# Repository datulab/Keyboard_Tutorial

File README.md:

# Keyboard_Tutorial
All the files needed to build your first DIY keyboard! 
Watch the videos here: https://youtu.be/ajjujZ0f_sk

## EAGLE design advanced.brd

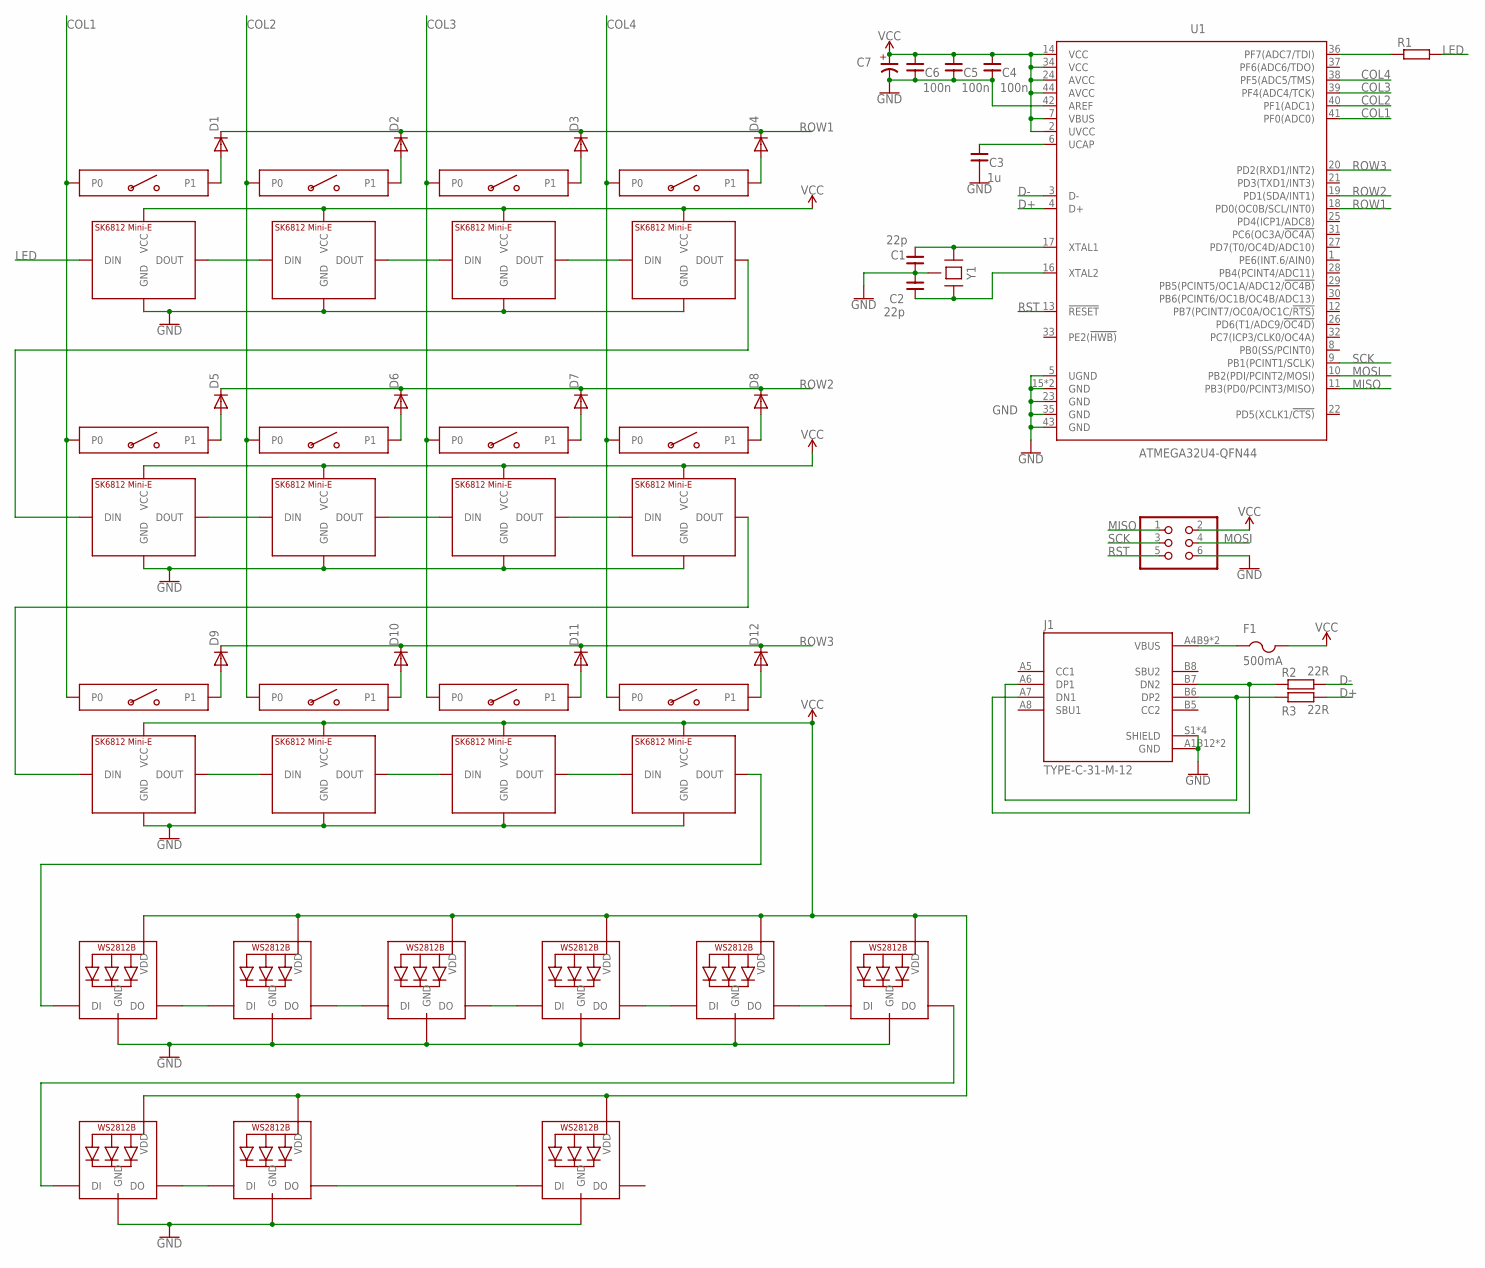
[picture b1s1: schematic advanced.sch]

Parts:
C1, C2: 22p; 0805
C3: 1u; 0805
C4, C5, C6: 100n; 0805
C7: 10u; 3216-18R/T
D1, D2, D3, D4, D5, D6, D7, D8, D9, D10, D11, D12: 1N4148DIODE_0805; 0805
F1: 500mA; R1206
J1: TYPE-C-31-M-12; HRO_TYPE-C-31-M-12
JP3: PINHD-2X3; 2X03
R1: RESISTOR-0805; R0805
R2, R3: 22R; R0805
U1: ATMEGA32U4-QFN44; QFN-44
U$1, U$2, U$3, U$4, U$5, U$6, U$7, U$8, U$10: WS2812B-3535; 3535-LED
U$55, U$57, U$59, U$61, U$73, U$75, U$77, U$79, U$91, U$93, U$95, U$97: KEYSWITCH-SK6812; UNIVERSAL_KEYSWITCH_SK6812MINIE
Y1: CRYSTAL-4PIN-3.2X2.5; CRYSTAL-3.2X2.5

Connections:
COL1: U1.41 (PF0(ADC0)), U$55.ALPS1 (P0), U$55.CHOC1 (P0), U$55.MX1 (P0), U$73.ALPS1 (P0), U$73.CHOC1 (P0), U$73.MX1 (P0), U$91.ALPS1 (P0), U$91.CHOC1 (P0), U$91.MX1 (P0)
COL2: U1.40 (PF1(ADC1)), U$57.ALPS1 (P0), U$57.CHOC1 (P0), U$57.MX1 (P0), U$75.ALPS1 (P0), U$75.CHOC1 (P0), U$75.MX1 (P0), U$93.ALPS1 (P0), U$93.CHOC1 (P0), U$93.MX1 (P0)
COL3: U1.39 (PF4(ADC4/TCK)), U$59.ALPS1 (P0), U$59.CHOC1 (P0), U$59.MX1 (P0), U$77.ALPS1 (P0), U$77.CHOC1 (P0), U$77.MX1 (P0), U$95.ALPS1 (P0), U$95.CHOC1 (P0), U$95.MX1 (P0)
COL4: U1.38 (PF5(ADC5/TMS)), U$61.ALPS1 (P0), U$61.CHOC1 (P0), U$61.MX1 (P0), U$79.ALPS1 (P0), U$79.CHOC1 (P0), U$79.MX1 (P0), U$97.ALPS1 (P0), U$97.CHOC1 (P0), U$97.MX1 (P0)
D+: R3.2, U1.4 (D+)
D-: R2.2, U1.3 (D-)
GND: C1.1, C2.2, C3.2, C4.2, C5.2, C6.2, C7.-, J1.A1B12 (GND), J1.B1A12 (GND), J1.S1 (SHIELD), J1.S2 (SHIELD), J1.S3 (SHIELD), J1.S4 (SHIELD), JP3.6, U1.5 (UGND), U1.15 (GND), U1.23 (GND), U1.35 (GND), U1.42 (AREF), U1.43 (GND), U1.TAB (GND), U$1.GND, U$2.GND, U$3.GND, U$4.GND, U$5.GND, U$6.GND, U$7.GND, U$8.GND, U$10.GND, U$55.GND, U$57.GND, U$59.GND, U$61.GND, U$73.GND, U$75.GND, U$77.GND, U$79.GND, U$91.GND, U$93.GND, U$95.GND, U$97.GND, Y1.2 (GND), Y1.4 (GND)
LED: R1.2, U$91.DIN
MISO: JP3.1, U1.11 (PB3(PD0/PCINT3/MISO))
MOSI: JP3.4, U1.10 (PB2(PDI/PCINT2/MOSI))
unnamed: U$1.P$4 (DO), U$2.P$3 (DI)
unnamed: U$2.P$4 (DO), U$3.P$3 (DI)
unnamed: U$3.P$4 (DO), U$4.P$3 (DI)
unnamed: U$4.P$4 (DO), U$5.P$3 (DI)
unnamed: U$5.P$4 (DO), U$6.P$3 (DI)
unnamed: U$7.P$4 (DO), U$8.P$3 (DI)
unnamed: U$8.P$4 (DO), U$10.P$3 (DI)
unnamed: U$6.P$4 (DO), U$7.P$3 (DI)
unnamed: U$1.P$3 (DI), U$61.DOUT
unnamed: C1.2, U1.17 (XTAL1), Y1.1
unnamed: F1.1, J1.A4B9 (VBUS), J1.B4A9 (VBUS)
unnamed: R1.1, U1.36 (PF7(ADC7/TDI))
unnamed: J1.A6 (DP1), J1.B6 (DP2), R3.1
unnamed: C2.1, U1.16 (XTAL2), Y1.3 (2)
unnamed: J1.A7 (DN1), J1.B7 (DN2), R2.1
unnamed: C3.1, U1.6 (UCAP)
unnamed: D9.1 (A), U$55.ALPS2 (P1), U$55.CHOC2 (P1), U$55.MX2 (P1)
unnamed: D10.1 (A), U$57.ALPS2 (P1), U$57.CHOC2 (P1), U$57.MX2 (P1)
unnamed: D11.1 (A), U$59.ALPS2 (P1), U$59.CHOC2 (P1), U$59.MX2 (P1)
unnamed: D12.1 (A), U$61.ALPS2 (P1), U$61.CHOC2 (P1), U$61.MX2 (P1)
unnamed: U$55.DOUT, U$57.DIN
unnamed: U$57.DOUT, U$59.DIN
unnamed: U$59.DOUT, U$61.DIN
unnamed: D5.1 (A), U$73.ALPS2 (P1), U$73.CHOC2 (P1), U$73.MX2 (P1)
unnamed: D6.1 (A), U$75.ALPS2 (P1), U$75.CHOC2 (P1), U$75.MX2 (P1)
unnamed: D7.1 (A), U$77.ALPS2 (P1), U$77.CHOC2 (P1), U$77.MX2 (P1)
unnamed: D8.1 (A), U$79.ALPS2 (P1), U$79.CHOC2 (P1), U$79.MX2 (P1)
unnamed: U$73.DOUT, U$75.DIN
unnamed: U$75.DOUT, U$77.DIN
unnamed: U$77.DOUT, U$79.DIN
unnamed: D1.1 (A), U$91.ALPS2 (P1), U$91.CHOC2 (P1), U$91.MX2 (P1)
unnamed: D2.1 (A), U$93.ALPS2 (P1), U$93.CHOC2 (P1), U$93.MX2 (P1)
unnamed: D3.1 (A), U$95.ALPS2 (P1), U$95.CHOC2 (P1), U$95.MX2 (P1)
unnamed: D4.1 (A), U$97.ALPS2 (P1), U$97.CHOC2 (P1), U$97.MX2 (P1)
unnamed: U$91.DOUT, U$93.DIN
unnamed: U$93.DOUT, U$95.DIN
unnamed: U$95.DOUT, U$97.DIN
unnamed: U$55.DIN, U$79.DOUT
unnamed: U$73.DIN, U$97.DOUT
ROW1: D1.2 (C), D2.2 (C), D3.2 (C), D4.2 (C), U1.18 (PD0(OC0B/SCL/INT0))
ROW2: D5.2 (C), D6.2 (C), D7.2 (C), D8.2 (C), U1.19 (PD1(SDA/INT1))
ROW3: D9.2 (C), D10.2 (C), D11.2 (C), D12.2 (C), U1.20 (PD2(RXD1/INT2))
RST: JP3.5, U1.13 (!RESET)
SCK: JP3.3, U1.9 (PB1(PCINT1/SCLK))
VCC: C4.1, C5.1, C6.1, C7.+, F1.2, JP3.2, U1.2 (UVCC), U1.7 (VBUS), U1.14 (VCC), U1.24 (AVCC), U1.34 (VCC), U1.44 (AVCC), U$1.VDD, U$2.VDD, U$3.VDD, U$4.VDD, U$5.VDD, U$6.VDD, U$7.VDD, U$8.VDD, U$10.VDD, U$55.VCC, U$57.VCC, U$59.VCC, U$61.VCC, U$73.VCC, U$75.VCC, U$77.VCC, U$79.VCC, U$91.VCC, U$93.VCC, U$95.VCC, U$97.VCC

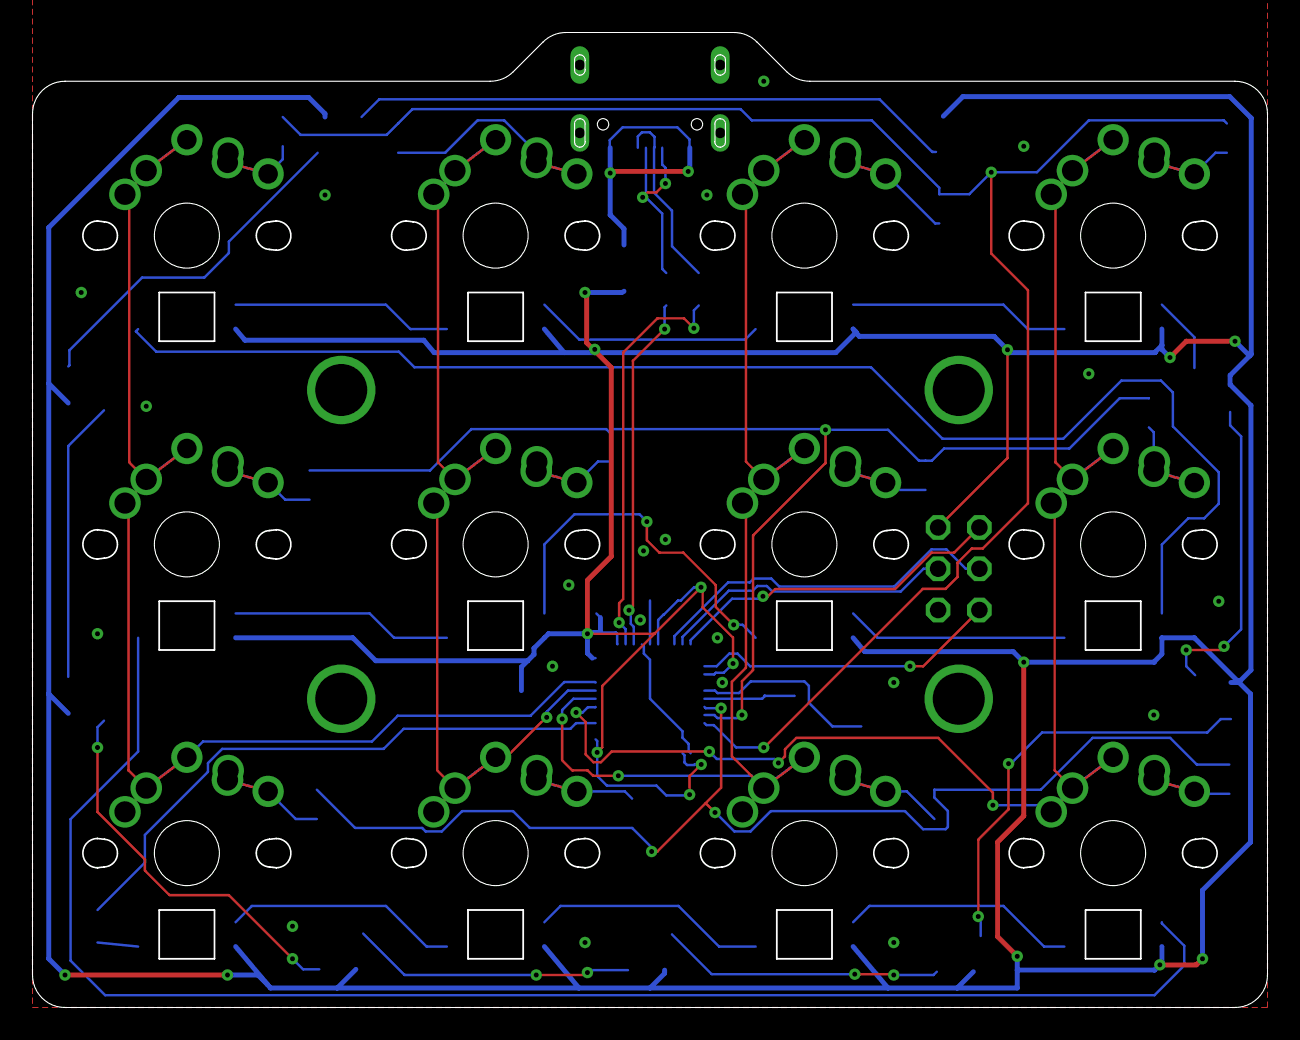
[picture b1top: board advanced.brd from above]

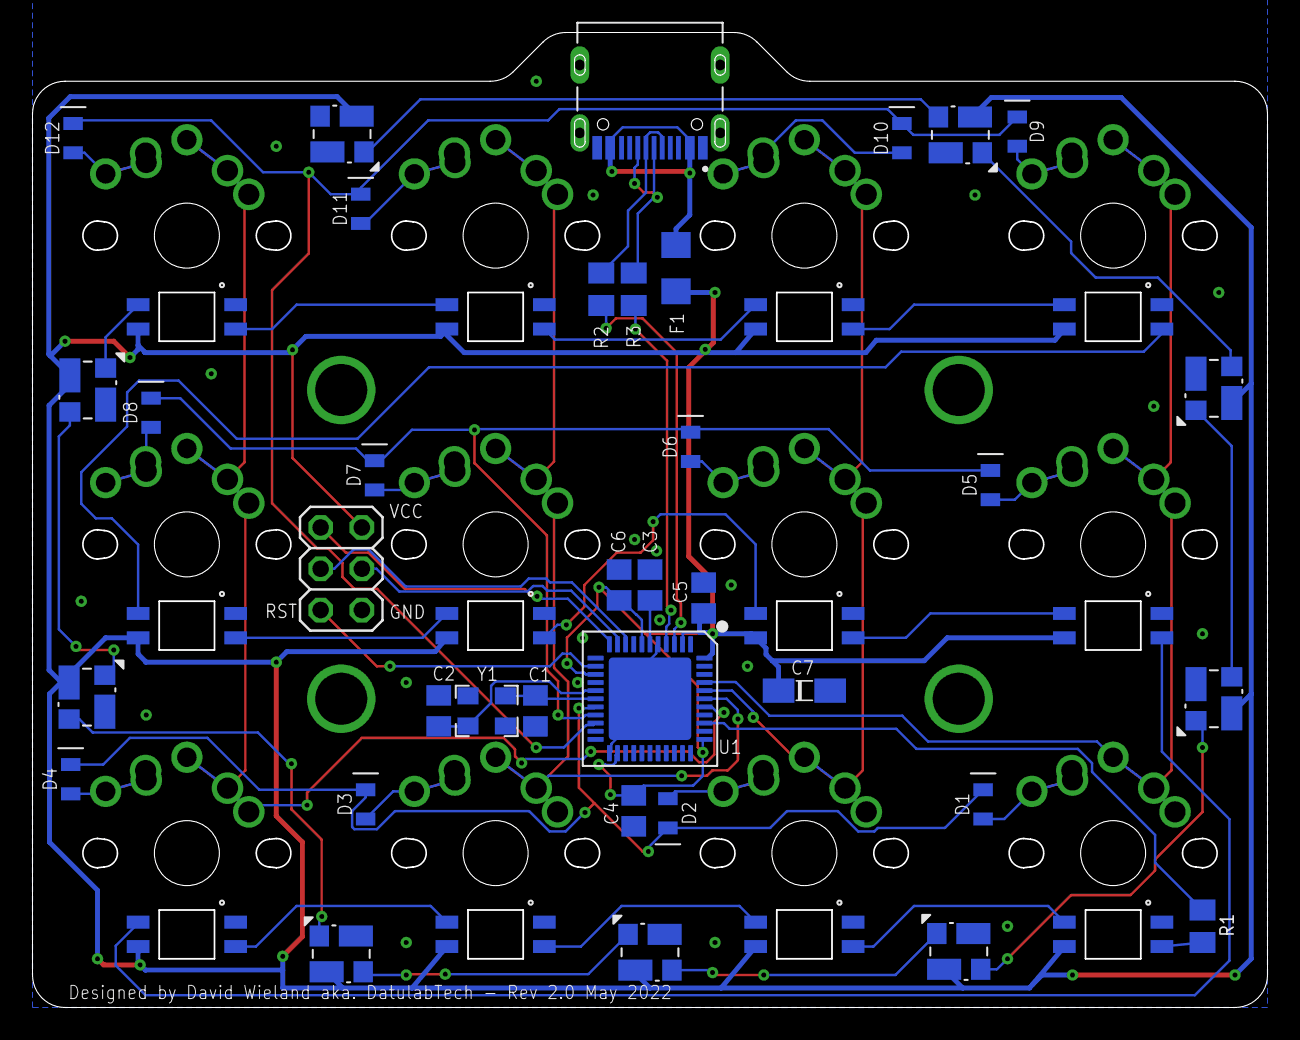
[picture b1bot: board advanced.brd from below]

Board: 2 copper layers, 75.9 x 59.9 mm, 48 parts (36 on the bottom side), 55 nets.

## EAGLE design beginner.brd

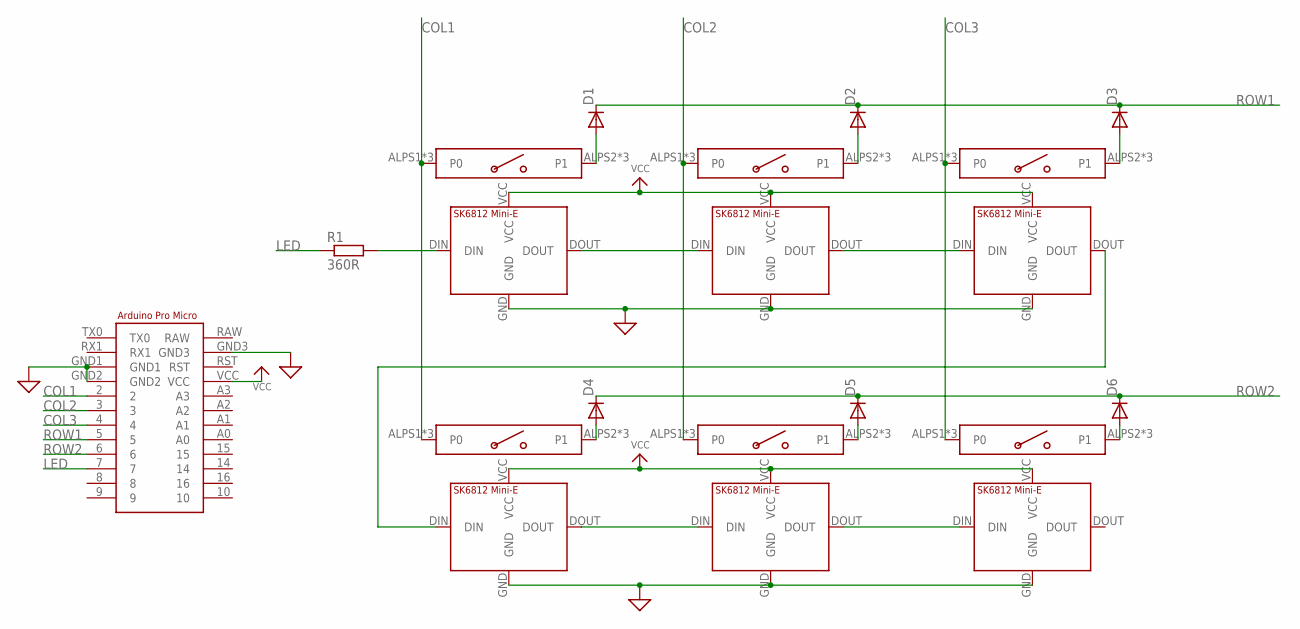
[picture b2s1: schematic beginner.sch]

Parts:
D1, D2, D3, D4, D5, D6: 1N41481N4148_THROUGH; DIODE-1N4148
R1: 360R; THT-RESISTOR
U$1: ARDUINO_PRO_MICRO
U$2, U$3, U$4, U$5, U$6, U$7: KEYSWITCH-SK6812; UNIVERSAL_KEYSWITCH_SK6812MINIE

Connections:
COL1: U$1.2, U$2.ALPS1 (P0), U$2.CHOC1 (P0), U$2.MX1 (P0), U$5.ALPS1 (P0), U$5.CHOC1 (P0), U$5.MX1 (P0)
COL2: U$1.3, U$3.ALPS1 (P0), U$3.CHOC1 (P0), U$3.MX1 (P0), U$6.ALPS1 (P0), U$6.CHOC1 (P0), U$6.MX1 (P0)
COL3: U$1.4, U$4.ALPS1 (P0), U$4.CHOC1 (P0), U$4.MX1 (P0), U$7.ALPS1 (P0), U$7.CHOC1 (P0), U$7.MX1 (P0)
GND: U$1.GND1, U$1.GND2, U$1.GND3, U$2.GND, U$3.GND, U$4.GND, U$5.GND, U$6.GND, U$7.GND
LED: R1.1, U$1.7
unnamed: U$2.DOUT, U$3.DIN
unnamed: U$3.DOUT, U$4.DIN
unnamed: D1.A, U$2.ALPS2 (P1), U$2.CHOC2 (P1), U$2.MX2 (P1)
unnamed: D2.A, U$3.ALPS2 (P1), U$3.CHOC2 (P1), U$3.MX2 (P1)
unnamed: D3.A, U$4.ALPS2 (P1), U$4.CHOC2 (P1), U$4.MX2 (P1)
unnamed: D4.A, U$5.ALPS2 (P1), U$5.CHOC2 (P1), U$5.MX2 (P1)
unnamed: U$5.DOUT, U$6.DIN
unnamed: U$6.DOUT, U$7.DIN
unnamed: D6.A, U$7.ALPS2 (P1), U$7.CHOC2 (P1), U$7.MX2 (P1)
unnamed: D5.A, U$6.ALPS2 (P1), U$6.CHOC2 (P1), U$6.MX2 (P1)
unnamed: U$4.DOUT, U$5.DIN
unnamed: R1.2, U$2.DIN
ROW1: D1.C, D2.C, D3.C, U$1.5
ROW2: D4.C, D5.C, D6.C, U$1.6
VCC: U$1.VCC, U$2.VCC, U$3.VCC, U$4.VCC, U$5.VCC, U$6.VCC, U$7.VCC

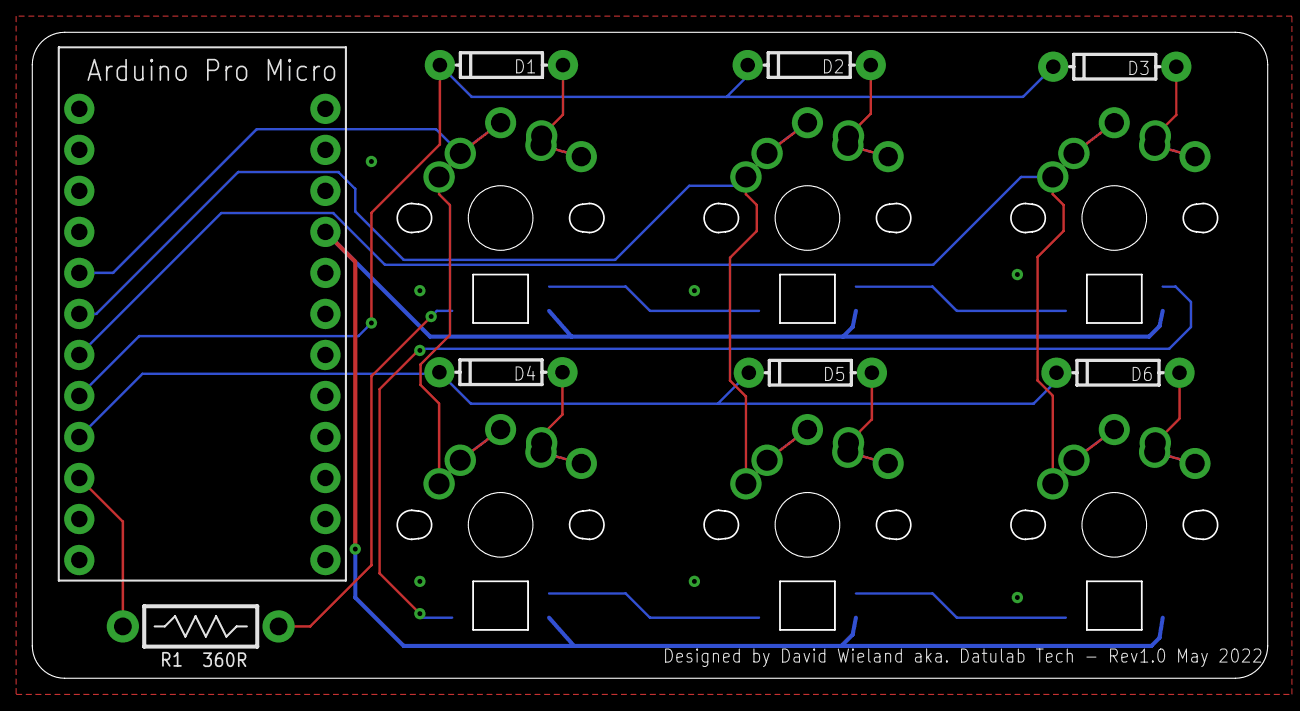
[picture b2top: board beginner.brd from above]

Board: 2 copper layers, 76.4 x 39.9 mm, 14 parts (0 on the bottom side), 20 nets.

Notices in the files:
parts and their libraries:
SparkFun-PowerSymbols: Licensing: Creative Commons ShareAlike 4.0 International - https://creativecommons.org/licenses/by-sa/4.0
